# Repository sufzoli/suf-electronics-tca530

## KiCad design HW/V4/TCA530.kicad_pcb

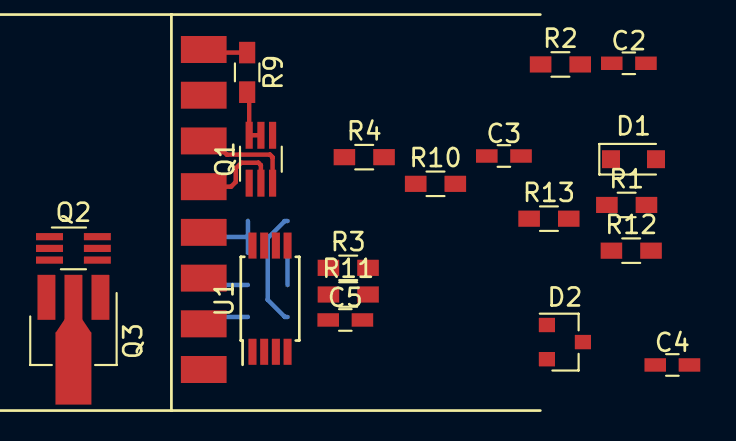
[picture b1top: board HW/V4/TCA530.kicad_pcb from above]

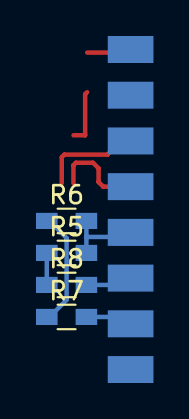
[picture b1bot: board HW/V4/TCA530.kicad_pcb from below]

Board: 2 copper layers, 24 parts (4 on the bottom side), 21 nets.

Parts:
C2: 1nF; C_0603_HandSoldering
C3: 1uF/35V; C_0603_HandSoldering
C4, C5: 1uF/50V; C_0603_HandSoldering
D1: PZU33V; D_SOD-323_HandSoldering
D2: TL431DBZ; SOT-23
J1: TCA530; CONN_EDGE_2,54_16
Q1, Q2: BC846BS; SOT-363_SC-70-6_Handsoldering
Q3: BCX53-16; SOT-89-3_Handsoldering
R1: 18K; R_0603_HandSoldering
R2: 100K; R_0603_HandSoldering
R3: 1K; R_0603_HandSoldering
R4, R13: 10K; R_0603_HandSoldering
R5, R6: 1M; R_0603_HandSoldering
R7, R8: 47K; R_0603_HandSoldering
R9: 15K; R_0603_HandSoldering
R10: 3,9K; R_0603_HandSoldering
R11: 19,1K; R_0603_HandSoldering
R12: 2,7K; R_0603_HandSoldering
U1: TL081; TSSOP-8_4.4x3mm_Pitch0.65mm

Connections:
+15V: J1.1, R9.1
AFC: C3.1, R3.1, R4.1, U1.5
AFC_IN+: J1.10, R7.2
AFC_IN-: J1.11, R8.2
FB: J1.8, U1.6
GND: C3.2, C4.2, C5.2, D1.2, D2.3, J1.12, J1.16, Q1.1, Q1.4, Q2.4, R5.2, R6.2, R12.2, U1.4
MUTE_CTRL: J1.4, Q1.2
MUTE_OUT: J1.3, Q1.3
unnamed: C2.1, R2.1, R4.2, U1.1
unnamed: C2.2, R2.2, R5.1, R8.1, U1.2
unnamed: C5.1, Q2.1, U1.8
unnamed: D1.1, Q2.2, R10.2
unnamed: D2.2, R11.2, R12.1
unnamed: Q1.5, Q1.6, R9.2
unnamed: Q2.3, R13.1
unnamed: Q2.5, U1.7
unnamed: Q3.1, R13.2
unnamed: R6.1, R7.1, U1.3
VIN: J1.5, Q2.6, Q3.2, R1.1, R10.1
Vo: C4.1, J1.6, Q3.3
Vref: D2.1, R1.2, R3.2, R11.1

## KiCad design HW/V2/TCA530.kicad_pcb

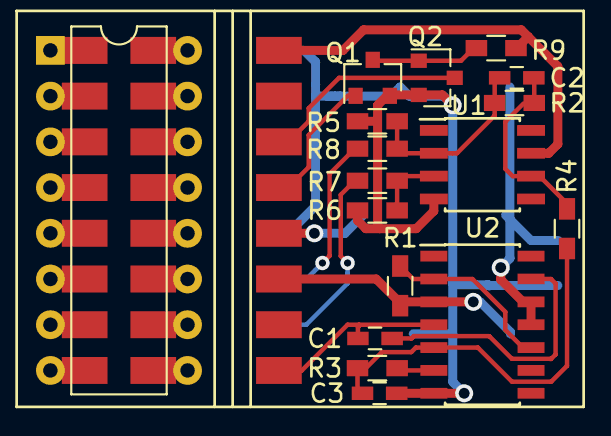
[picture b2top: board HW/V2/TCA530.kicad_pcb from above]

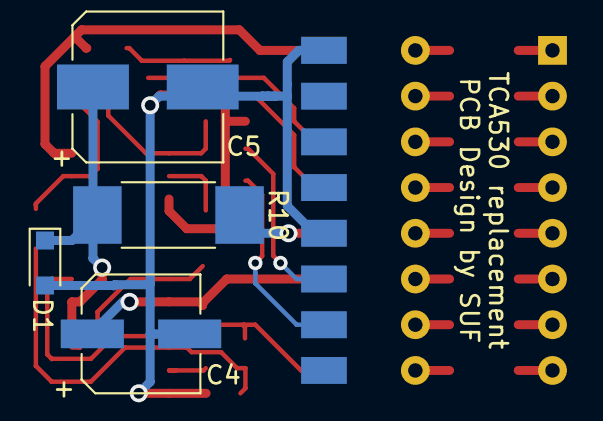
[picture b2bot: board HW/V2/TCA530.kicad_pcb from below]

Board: 2 copper layers, 23 parts (4 on the bottom side), 34 nets.

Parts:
C1: 100pF; C_0603_HandSoldering
C2: 1nF; C_0603_HandSoldering
C3: 10uF/16V; C_0603_HandSoldering
C4: 10uF/50V; CP_Elec_6.3x5.3
C5: 47uF/50V; CP_Elec_8x10
D1: PZU33V; D_SOD-323_HandSoldering
J1: TCA530; CONN_EDGE_2,54_16
J2: TCA530; DIP-16_W7.62mm
J3: TCA530; CONN_EDGE_SOLDER_2,54_16
Q1, Q2: BC846B; SOT-23
R1: 6R8; R_0603_HandSoldering
R2: 100K; R_0603_HandSoldering
R3: 1K; R_0603_HandSoldering
R4: 10K; R_0603_HandSoldering
R5, R6: 1M; R_0603_HandSoldering
R7, R8: 47K; R_0603_HandSoldering
R9: 15K; R_0603_HandSoldering
R10: 0; R_2512_HandSoldering
U1: TL081; SOIC-8_3.9x4.9mm_Pitch1.27mm
U2: LM723; SOIC-14_3.9x8.7mm_Pitch1.27mm

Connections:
+15V: J1.1, R9.1, U1.7
AFC: C3.1, R3.1, R4.1, U2.5
AFC_IN+: J1.10, R7.2
AFC_IN-: J1.11, R8.2
FB: C1.2, J1.8, U2.4
GND: C3.2, C4.2, C5.2, D1.2, J1.12, J1.16, Q1.2, Q2.2, R5.2, R6.2, U1.4, U2.7
MUTE_CTRL: J1.4, Q1.1
MUTE_OUT: J1.3, Q2.3
unnamed: C1.1, U2.13
unnamed: C2.1, R2.1, R4.2, U1.6
unnamed: C2.2, R2.2, R5.1, R8.1, U1.2
unnamed: J1.5, R10.2
unnamed: J2.1, J3.1
unnamed: J2.2, J3.2
unnamed: J2.3, J3.3
unnamed: J2.4, J3.4
unnamed: J2.5, J3.5
unnamed: J2.6, J3.6
unnamed: J2.7, J3.7
unnamed: J2.8, J3.8
unnamed: J2.9, J3.9
unnamed: J2.10, J3.10
unnamed: J2.11, J3.11
unnamed: J2.12, J3.12
unnamed: J2.13, J3.13
unnamed: J2.14, J3.14
unnamed: J2.15, J3.15
unnamed: J2.16, J3.16
unnamed: Q1.3, Q2.1, R9.2
unnamed: R1.1, U2.2, U2.10
unnamed: R3.2, U2.6
unnamed: R6.1, R7.1, U1.3
VCC: C5.1, D1.1, R10.1, U2.11, U2.12
Vo: C4.1, J1.6, R1.2, U2.3

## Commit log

2019-03-20 BOM Added
2021-03-20 New versions addeed
